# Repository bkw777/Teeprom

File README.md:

These are all virtual UV EPROMS / virtual mask roms, using electrically programmable EEPROM, FRAM, or FLASH with the pinout adapted to work in place of 27Cxx UV/OTP EPROMS or standard mask roms, on a specially shaped PCB and 3d-printed carrier to create a virtual Molex 78802 module to fit inside a Molex 78805 socket.

# Teeprom

[Teeprom](http://tandy.wiki/Teeprom) is an EEPROM module for Tandy Model 100, 102, & 200 portable computers.

# Meeprom

[Meeprom](http://tandy.wiki/Meeprom) is an EEPROM module for any other Molex 78805 socket that expects a 27C256 or standard mask rom chip. Not for Model 100/200. Examples: Tandy Model 600, Kyotronic KC-85, Epson PX-4, PX-8, handheld terminals like Intermec 9440, various industrial equipment like Allen Bradley SLC-500 PLCs, etc.

# MEE2732
Virtual 27C32 & virtual Molex 78802 carrier  

[MEE2732](MEE2732.md)  
24-pin 2732 pinout

# M4ROM
[M4ROM](https://github.com/bkw777/M4ROM)  
Version of Teeprom & Meeprom that uses a 29F010 flash instead of a 28C256 eeprom, and provides 4 32k rom images.

# References
[Molex78802_Module](https://github.com/bkw777/Molex78802_Module)

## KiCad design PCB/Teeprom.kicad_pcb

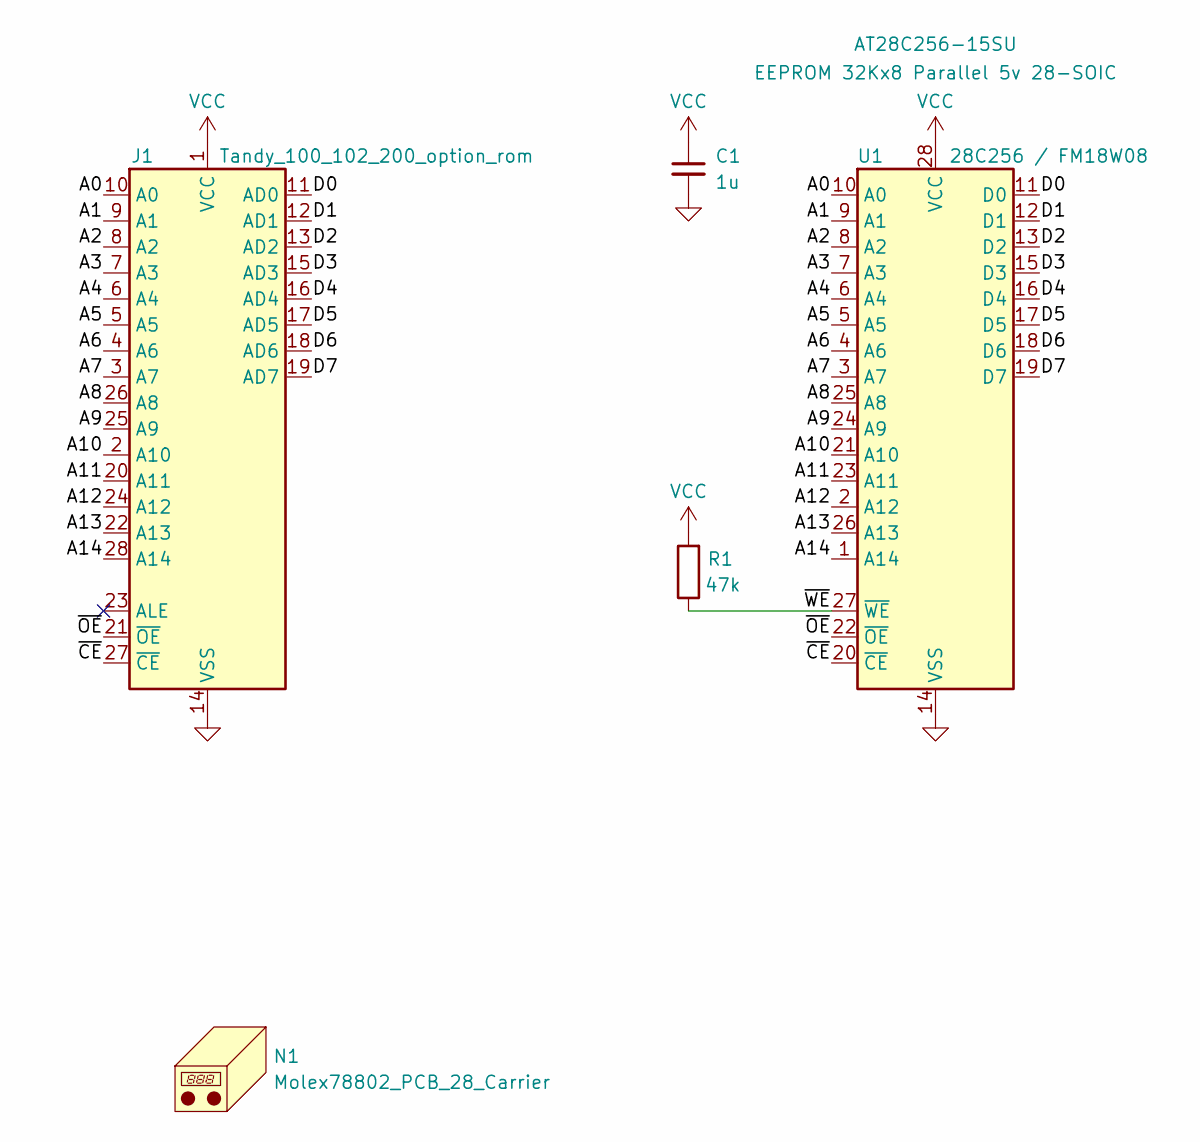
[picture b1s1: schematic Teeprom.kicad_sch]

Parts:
C1: 1u; C_0805; MPN CL21B105KAFNNNE
J1: Tandy_100_102_200_option_rom; Molex78802_PCB_28
N1: Molex78802_PCB_28_Carrier
R1: 47k; R_0805; MPN CRCW080547K0FKEA
U1: 28C256 / FM18W08; SOIC-28W; MPN AT28C256-15SU

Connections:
/A0: J1.10 (A0), U1.10 (A0)
/A1: J1.9 (A1), U1.9 (A1)
/A2: J1.8 (A2), U1.8 (A2)
/A3: J1.7 (A3), U1.7 (A3)
/A4: J1.6 (A4), U1.6 (A4)
/A5: J1.5 (A5), U1.5 (A5)
/A6: J1.4 (A6), U1.4 (A6)
/A7: J1.3 (A7), U1.3 (A7)
/A8: J1.26 (A8), U1.25 (A8)
/A9: J1.25 (A9), U1.24 (A9)
/A10: J1.2 (A10), U1.21 (A10)
/A11: J1.20 (A11), U1.23 (A11)
/A12: J1.24 (A12), U1.2 (A12)
/A13: J1.22 (A13), U1.26 (A13)
/A14: J1.28 (A14), U1.1 (A14)
/D0: J1.11 (AD0), U1.11 (D0)
/D1: J1.12 (AD1), U1.12 (D1)
/D2: J1.13 (AD2), U1.13 (D2)
/D3: J1.15 (AD3), U1.15 (D3)
/D4: J1.16 (AD4), U1.16 (D4)
/D5: J1.17 (AD5), U1.17 (D5)
/D6: J1.18 (AD6), U1.18 (D6)
/D7: J1.19 (AD7), U1.19 (D7)
/~CE: J1.27 (~CE), U1.20 (~CE)
/~OE: J1.21 (~OE), U1.22 (~OE)
/~WE: R1.1, U1.27 (~WE)
GND: C1.2, J1.14 (VSS), U1.14 (VSS)
VCC: C1.1, J1.1 (VCC), R1.2, U1.28 (VCC)

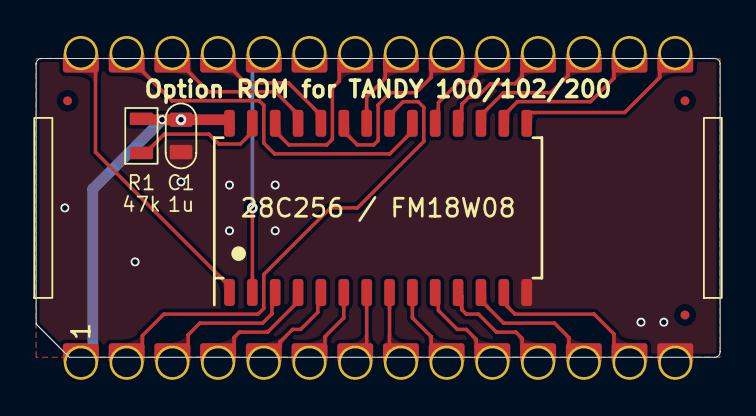
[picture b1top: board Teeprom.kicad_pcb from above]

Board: 2 copper layers, 38.0 x 16.6 mm, 5 parts (0 on the bottom side), 28 nets.

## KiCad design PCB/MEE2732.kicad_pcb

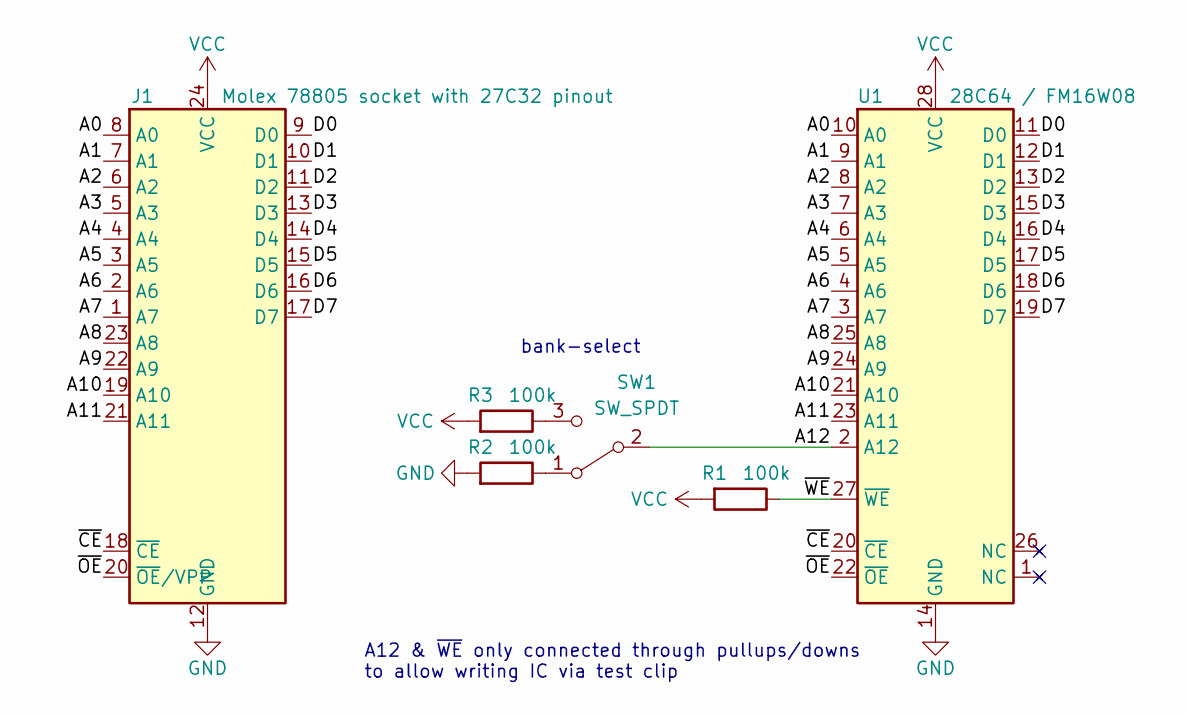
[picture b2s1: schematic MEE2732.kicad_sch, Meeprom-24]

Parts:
J1: Molex 78805 socket with 27C32 pinout; Molex78802_PCB_24
R1, R2, R3: 100k; R_0805
SW1: SW_SPDT; CL-SB-12C-0x
U1: 28C64 / FM16W08; SOIC-28W

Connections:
/A0: J1.8 (A0), U1.10 (A0)
/A1: J1.7 (A1), U1.9 (A1)
/A2: J1.6 (A2), U1.8 (A2)
/A3: J1.5 (A3), U1.7 (A3)
/A4: J1.4 (A4), U1.6 (A4)
/A5: J1.3 (A5), U1.5 (A5)
/A6: J1.2 (A6), U1.4 (A6)
/A7: J1.1 (A7), U1.3 (A7)
/A8: J1.23 (A8), U1.25 (A8)
/A9: J1.22 (A9), U1.24 (A9)
/A10: J1.19 (A10), U1.21 (A10)
/A11: J1.21 (A11), U1.23 (A11)
/A12: SW1.2 (B), U1.2 (A12)
/D0: J1.9 (D0), U1.11 (D0)
/D1: J1.10 (D1), U1.12 (D1)
/D2: J1.11 (D2), U1.13 (D2)
/D3: J1.13 (D3), U1.15 (D3)
/D4: J1.14 (D4), U1.16 (D4)
/D5: J1.15 (D5), U1.17 (D5)
/D6: J1.16 (D6), U1.18 (D6)
/D7: J1.17 (D7), U1.19 (D7)
/~CE: J1.18 (~CE), U1.20 (~CE)
/~OE: J1.20 (~OE/VPP), U1.22 (~OE)
/~WE: R1.1, U1.27 (~WE)
GND: J1.12 (GND), R2.2, U1.14 (GND)
unnamed: R2.1, SW1.1 (A)
unnamed: R3.1, SW1.3 (C)
VCC: J1.24 (VCC), R1.2, R3.2, U1.28 (VCC)

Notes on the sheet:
bank-select
A12 & ~{WE} only connected through pullups/downs to allow writing IC via test clip

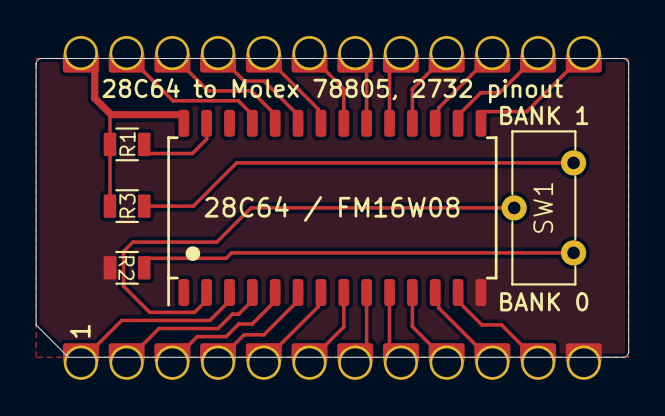
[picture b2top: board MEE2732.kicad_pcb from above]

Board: 2 copper layers, 32.9 x 16.6 mm, 6 parts (0 on the bottom side), 28 nets.

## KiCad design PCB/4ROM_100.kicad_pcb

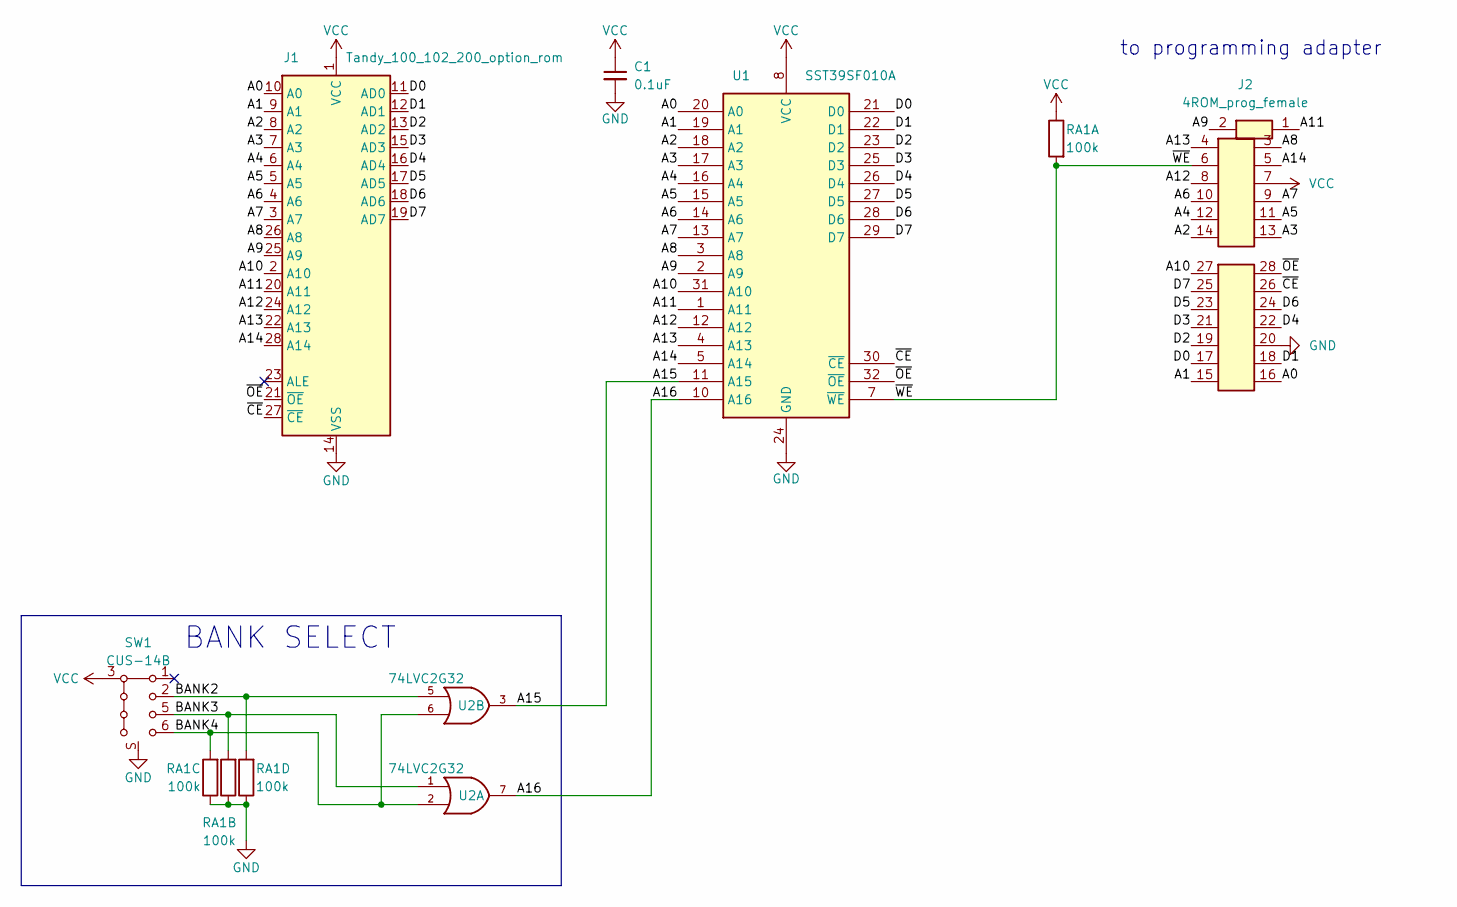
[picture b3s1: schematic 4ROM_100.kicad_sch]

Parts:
C1: 0.1uF; C_0805
J1: Tandy_100_102_200_option_rom; Molex78802_PCB_28
J2: 4ROM_prog_female
RA1: 100k; R_Array_Convex_4x0612
SW1: CUS-14B; SW_SP4T_CUS-14B
U1: SST39SF010A; TSOP32-14mm
U2: 74LVC2G32; TSSOP-8_3x3mm_P0.65mm

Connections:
/A0: J1.10 (A0), J2.16 (A0), U1.20 (A0)
/A1: J1.9 (A1), J2.15 (A1), U1.19 (A1)
/A2: J1.8 (A2), J2.14 (A2), U1.18 (A2)
/A3: J1.7 (A3), J2.13 (A3), U1.17 (A3)
/A4: J1.6 (A4), J2.12 (A4), U1.16 (A4)
/A5: J1.5 (A5), J2.11 (A5), U1.15 (A5)
/A6: J1.4 (A6), J2.10 (A6), U1.14 (A6)
/A7: J1.3 (A7), J2.9 (A7), U1.13 (A7)
/A8: J1.26 (A8), J2.3 (A8), U1.3 (A8)
/A9: J1.25 (A9), J2.2 (A9), U1.2 (A9)
/A10: J1.2 (A10), J2.27 (A10), U1.31 (A10)
/A11: J1.20 (A11), J2.1 (A11), U1.1 (A11)
/A12: J1.24 (A12), J2.8 (A12), U1.12 (A12)
/A13: J1.22 (A13), J2.4 (A13), U1.4 (A13)
/A14: J1.28 (A14), J2.5 (A14), U1.5 (A14)
/A15: U1.11 (A15), U2.3
/A16: U1.10 (A16), U2.7
/BANK2: RA1.4 (R4.1), SW1.2, U2.5
/BANK3: RA1.2 (R2.1), SW1.5, U2.1
/BANK4: RA1.3 (R3.1), SW1.6, U2.2, U2.6
/D0: J1.11 (AD0), J2.17 (D0), U1.21 (D0)
/D1: J1.12 (AD1), J2.18 (D1), U1.22 (D1)
/D2: J1.13 (AD2), J2.19 (D2), U1.23 (D2)
/D3: J1.15 (AD3), J2.21 (D3), U1.25 (D3)
/D4: J1.16 (AD4), J2.22 (D4), U1.26 (D4)
/D5: J1.17 (AD5), J2.23 (D5), U1.27 (D5)
/D6: J1.18 (AD6), J2.24 (D6), U1.28 (D6)
/D7: J1.19 (AD7), J2.25 (D7), U1.29 (D7)
/~CE: J1.27 (~CE), J2.26 (~CE), U1.30 (~CE)
/~OE: J1.21 (~OE), J2.28 (~OE), U1.32 (~OE)
/~WE: J2.6 (~WE), RA1.1 (R1.1), U1.7 (~WE)
GND: C1.2, J1.14 (VSS), J2.20 (GND), RA1.5 (R4.2), RA1.6 (R3.2), RA1.7 (R2.2), SW1.S, U1.24 (GND), U2.4 (GND)
VCC: C1.1, J1.1 (VCC), J2.7 (VCC), RA1.8 (R1.2), SW1.3 (C), SW1.4 (C), U1.8 (VCC), U2.8 (VCC)

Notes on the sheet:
BANK SELECT
to programming adapter

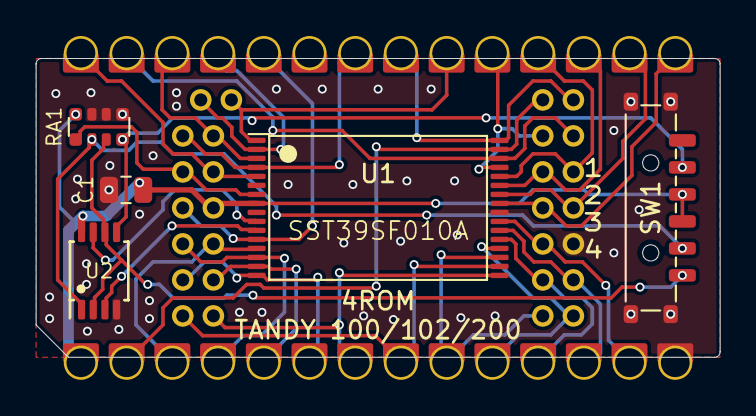
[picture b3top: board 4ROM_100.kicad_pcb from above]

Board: 2 copper layers, 38.0 x 16.6 mm, 7 parts (0 on the bottom side), 33 nets.

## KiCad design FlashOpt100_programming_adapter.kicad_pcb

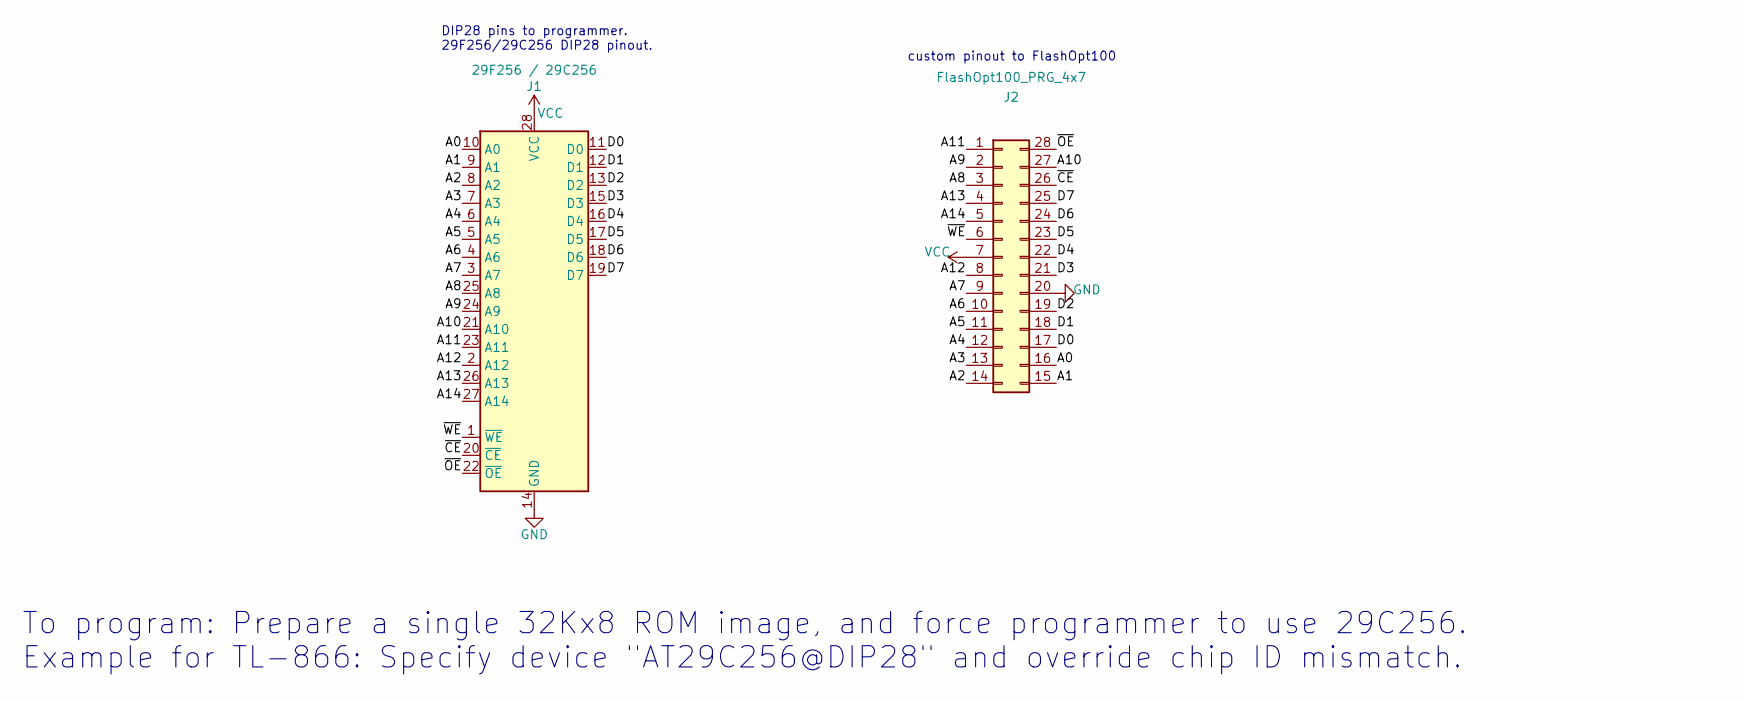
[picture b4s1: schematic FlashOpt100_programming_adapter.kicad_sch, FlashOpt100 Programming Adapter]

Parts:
J1: 29F256 / 29C256; DIP-28_600
J2: FlashOpt100_PRG_4x7; FlashOpt100_PRG_4x7_male

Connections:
/A0: J1.10 (A0), J2.16
/A1: J1.9 (A1), J2.15
/A2: J1.8 (A2), J2.14
/A3: J1.7 (A3), J2.13
/A4: J1.6 (A4), J2.12
/A5: J1.5 (A5), J2.11
/A6: J1.4 (A6), J2.10
/A7: J1.3 (A7), J2.9
/A8: J1.25 (A8), J2.3
/A9: J1.24 (A9), J2.2
/A10: J1.21 (A10), J2.27
/A11: J1.23 (A11), J2.1
/A12: J1.2 (A12), J2.8
/A13: J1.26 (A13), J2.4
/A14: J1.27 (A14), J2.5
/D0: J1.11 (D0), J2.17
/D1: J1.12 (D1), J2.18
/D2: J1.13 (D2), J2.19
/D3: J1.15 (D3), J2.21
/D4: J1.16 (D4), J2.22
/D5: J1.17 (D5), J2.23
/D6: J1.18 (D6), J2.24
/D7: J1.19 (D7), J2.25
/~CE: J1.20 (~CE), J2.26
/~OE: J1.22 (~OE), J2.28
/~WE: J1.1 (~WE), J2.6
GND: J1.14 (GND), J2.20
VCC: J1.28 (VCC), J2.7

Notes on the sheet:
custom pinout to FlashOpt100
To program: Prepare a single 32Kx8 ROM image, and force programmer to use 29C256. Example for TL-866: Specify device "AT29C256@DIP28" and override chip ID mismatch.
DIP28 pins to programmer. 29F256/29C256 DIP28 pinout.

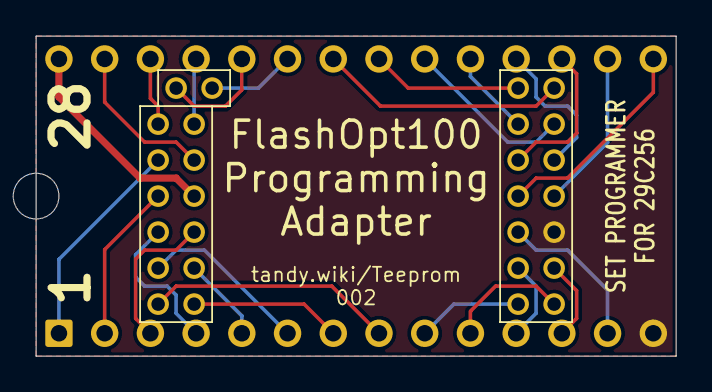
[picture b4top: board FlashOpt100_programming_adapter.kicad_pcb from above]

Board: 2 copper layers, 35.6 x 17.8 mm, 3 parts (0 on the bottom side), 28 nets.

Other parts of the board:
notch: IC_polarity_notch

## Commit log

2019-08-24 initial
2019-08-24 add readme
2019-09-09 update to new pcb2molex8878 template & carrier with chamfer instead of pin
2020-02-29 update to latest pcb2molex8878 pcb dimensions and carrier model
2020-03-08 Change license to CC. Add Meeprom. Add copper pours.
2020-03-08 gitignore
2020-03-08 improve pour
2020-03-08 improve ground paths in pours
2020-03-10 lock virtual footprint for carrier, set page title
2020-10-06 gitignore, remove explicit gnd trace
2020-10-23 minor
2020-10-23 Teeprom 2.0 the overkilling (new board FlashOpt100)
2020-10-23 remove sharp inside angle vcc & r1
2020-10-23 remove junk file
2020-10-23 FlashRom100 programming socket
2020-10-23 FlashOpt100 programming port
2020-10-23 programming adapter
2020-10-24 readme
2020-11-01 flashopt100 prg holes alignment, prg adapter dip holes size
2020-11-01 flashopt100 prg routing & text
2020-11-01 renders
2020-11-08 adjust some footprints and remove flashopt100 programming adapter from readme
2020-11-09 completely new FlashOpt100 and programming adapter
2020-11-09 FlashOpt100 remove zone fill
2020-11-09 silkscreen
2021-05-10 cosmetics
2021-05-23 cleanup files
2021-05-23 update to v004 board outline and carrier
2021-05-25 silkscreens
2021-05-30 add MEE2732
2021-05-30 MEE2732 readme
2021-05-30 spurious leftover trace on Meeprom
2022-12-24 kicad 6, flashopt100 programming socket
2022-12-24 FlashOpt100 pics
2022-12-24 MEE2732 minor tidy up
2023-01-10 add FRAM to silkscreen, rename FlashOpt100 to 4ROM_100, fix 4ROM programming adapter, add 4ROM_STD
2023-02-13 4ROM_78802 and programming adapter are now tested and verified
2023-02-13 4ROM_78802 and 4ROM programming adapter BOM & PCB links
2023-02-21 4ROM_100 pcb url
2023-02-21 4ROM_100 readme
2023-02-21 4ROM pic
2023-02-21 4ROM programmer notes
2023-02-26 cosmetic schematic touchups
2023-09-04 kicad 7, renders, reoganize files
2023-09-04 render
2023-12-31 split off 4ROM to it's own repo
2026-02-23 add caps & fiducials, remove dead shapeways links

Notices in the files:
4ROM_100.kicad_sch:
CC-BY-SA
